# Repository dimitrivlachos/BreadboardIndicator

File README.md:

# Bread Board Indicator

This is a simple PCB design that adds a row of 30 LEDs to a breadboard in order to easily view microcontroller outputs (Or any outputs really).

## PCB
<table>
  <tr>
    <td></td><td></td>
  </tr>
 </table>

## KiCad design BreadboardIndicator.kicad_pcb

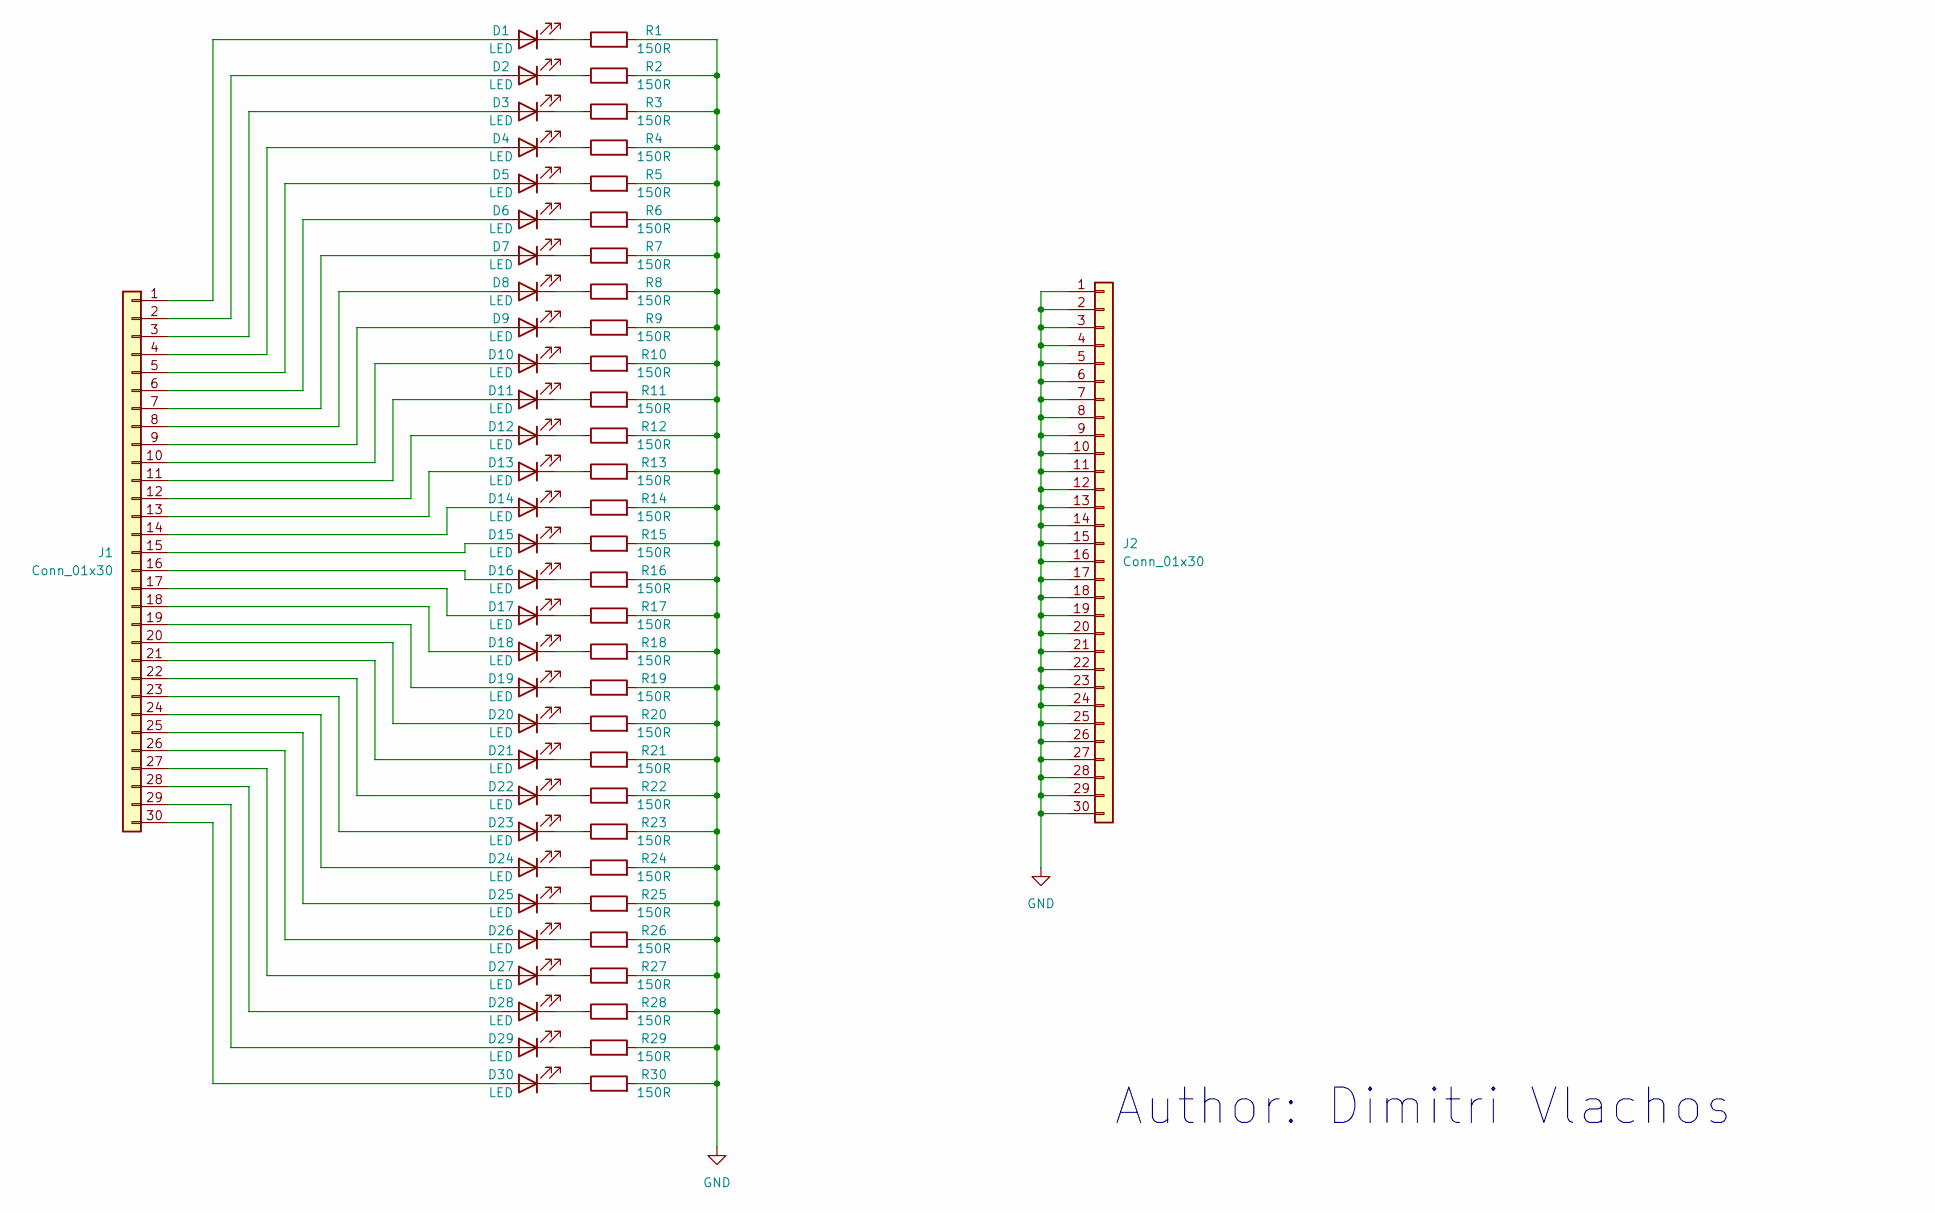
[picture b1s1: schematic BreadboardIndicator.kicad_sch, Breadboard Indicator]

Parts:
D1, D2, D3, D4, D5, D6, D7, D8, D9, D10, D11, D12, D13, D14, D15, D16, D17, D18, D19, D20, D21, D22, D23, D24, D25, D26, D27, D28, D29, D30: LED; LED_0805_2012Metric
J1, J2: Conn_01x30; PinHeader_1x30_P2.54mm_Vertical
R1, R2, R3, R4, R5, R6, R7, R8, R9, R10, R11, R12, R13, R14, R15, R16, R17, R18, R19, R20, R21, R22, R23, R24, R25, R26, R27, R28, R29, R30: 150R; R_0805_2012Metric

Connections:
GND: J2.1, J2.2, J2.3, J2.4, J2.5, J2.6, J2.7, J2.8, J2.9, J2.10, J2.11, J2.12, J2.13, J2.14, J2.15, J2.16, J2.17, J2.18, J2.19, J2.20, J2.21, J2.22, J2.23, J2.24, J2.25, J2.26, J2.27, J2.28, J2.29, J2.30, R1.2, R2.2, R3.2, R4.2, R5.2, R6.2, R7.2, R8.2, R9.2, R10.2, R11.2, R12.2, R13.2, R14.2, R15.2, R16.2, R17.2, R18.2, R19.2, R20.2, R21.2, R22.2, R23.2, R24.2, R25.2, R26.2, R27.2, R28.2, R29.2, R30.2; also elsewhere on the board
unnamed 1: D1.2 (A), J1.1; also elsewhere on the board
unnamed: D1.1 (K), R1.1
unnamed 3: D2.2 (A), J1.2; also elsewhere on the board
unnamed: D2.1 (K), R2.1
unnamed 5: D3.2 (A), J1.3; also elsewhere on the board
unnamed: D3.1 (K), R3.1
unnamed 7: D4.2 (A), J1.4; also elsewhere on the board
unnamed: D4.1 (K), R4.1
unnamed 9: D5.2 (A), J1.5; also elsewhere on the board
unnamed: D5.1 (K), R5.1
unnamed 11: D6.2 (A), J1.6; also elsewhere on the board
unnamed: D6.1 (K), R6.1
unnamed 13: D7.2 (A), J1.7; also elsewhere on the board
unnamed: D7.1 (K), R7.1
unnamed 15: D8.2 (A), J1.8; also elsewhere on the board
unnamed: D8.1 (K), R8.1
unnamed 17: D9.2 (A), J1.9; also elsewhere on the board
unnamed: D9.1 (K), R9.1
unnamed 19: D10.2 (A), J1.10; also elsewhere on the board
unnamed: D10.1 (K), R10.1
unnamed 21: D11.2 (A), J1.11; also elsewhere on the board
unnamed: D11.1 (K), R11.1
unnamed 23: D12.2 (A), J1.12; also elsewhere on the board
unnamed: D12.1 (K), R12.1
unnamed 25: D13.2 (A), J1.13; also elsewhere on the board
unnamed: D13.1 (K), R13.1
unnamed 27: D14.2 (A), J1.14; also elsewhere on the board
unnamed: D14.1 (K), R14.1
unnamed 29: D15.2 (A), J1.15; also elsewhere on the board
unnamed: D15.1 (K), R15.1
unnamed 31: D16.2 (A), J1.16; also elsewhere on the board
unnamed: D16.1 (K), R16.1
unnamed 33: D17.2 (A), J1.17; also elsewhere on the board
unnamed: D17.1 (K), R17.1
unnamed 35: D18.2 (A), J1.18; also elsewhere on the board
unnamed: D18.1 (K), R18.1
unnamed 37: D19.2 (A), J1.19; also elsewhere on the board
unnamed: D19.1 (K), R19.1
unnamed 39: D20.2 (A), J1.20; also elsewhere on the board
unnamed: D20.1 (K), R20.1
unnamed 41: D21.2 (A), J1.21; also elsewhere on the board
unnamed: D21.1 (K), R21.1
unnamed 43: D22.2 (A), J1.22; also elsewhere on the board
unnamed: D22.1 (K), R22.1
unnamed 45: D23.2 (A), J1.23; also elsewhere on the board
unnamed: D23.1 (K), R23.1
unnamed 47: D24.2 (A), J1.24; also elsewhere on the board
unnamed: D24.1 (K), R24.1
unnamed 49: D25.2 (A), J1.25; also elsewhere on the board
unnamed: D25.1 (K), R25.1
unnamed 51: D26.2 (A), J1.26; also elsewhere on the board
unnamed: D26.1 (K), R26.1
unnamed 53: D27.2 (A), J1.27; also elsewhere on the board
unnamed: D27.1 (K), R27.1
unnamed 55: D28.2 (A), J1.28; also elsewhere on the board
unnamed: D28.1 (K), R28.1
unnamed 57: D29.2 (A), J1.29; also elsewhere on the board
unnamed: D29.1 (K), R29.1
unnamed 59: D30.2 (A), J1.30; also elsewhere on the board
unnamed: D30.1 (K), R30.1

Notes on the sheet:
Author: Dimitri Vlachos

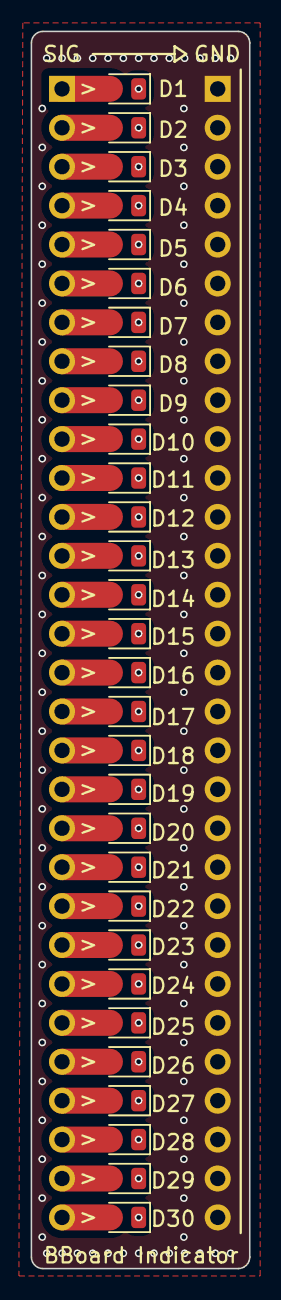
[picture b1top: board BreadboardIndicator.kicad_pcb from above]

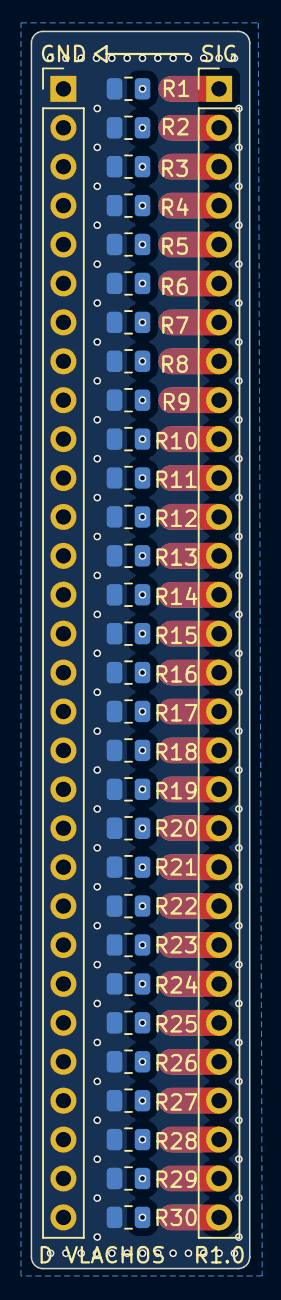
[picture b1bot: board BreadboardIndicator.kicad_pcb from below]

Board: 2 copper layers, 14.2 x 80.8 mm, 62 parts (32 on the bottom side), 61 nets.

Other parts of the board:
GND: Conn_01x30; PinHeader_1x30_P2.54mm_Vertical
SIG: Conn_01x30; PinHeader_1x30_P2.54mm_Vertical

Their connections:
GND: GND.1, GND.2, GND.3, GND.4, GND.5, GND.6, GND.7, GND.8, GND.9, GND.10, GND.11, GND.12, GND.13, GND.14, GND.15, GND.16, GND.17, GND.18, GND.19, GND.20, GND.21, GND.22, GND.23, GND.24, GND.25, GND.26, GND.27, GND.28, GND.29, GND.30; also elsewhere on the board
unnamed 1: SIG.1; also elsewhere on the board
unnamed 3: SIG.2; also elsewhere on the board
unnamed 5: SIG.3; also elsewhere on the board
unnamed 7: SIG.4; also elsewhere on the board
unnamed 9: SIG.5; also elsewhere on the board
unnamed 11: SIG.6; also elsewhere on the board
unnamed 13: SIG.7; also elsewhere on the board
unnamed 15: SIG.8; also elsewhere on the board
unnamed 17: SIG.9; also elsewhere on the board
unnamed 19: SIG.10; also elsewhere on the board
unnamed 21: SIG.11; also elsewhere on the board
unnamed 23: SIG.12; also elsewhere on the board
unnamed 25: SIG.13; also elsewhere on the board
unnamed 27: SIG.14; also elsewhere on the board
unnamed 29: SIG.15; also elsewhere on the board
unnamed 31: SIG.16; also elsewhere on the board
unnamed 33: SIG.17; also elsewhere on the board
unnamed 35: SIG.18; also elsewhere on the board
unnamed 37: SIG.19; also elsewhere on the board
unnamed 39: SIG.20; also elsewhere on the board
unnamed 41: SIG.21; also elsewhere on the board
unnamed 43: SIG.22; also elsewhere on the board
unnamed 45: SIG.23; also elsewhere on the board
unnamed 47: SIG.24; also elsewhere on the board
unnamed 49: SIG.25; also elsewhere on the board
unnamed 51: SIG.26; also elsewhere on the board
unnamed 53: SIG.27; also elsewhere on the board
unnamed 55: SIG.28; also elsewhere on the board
unnamed 57: SIG.29; also elsewhere on the board
unnamed 59: SIG.30; also elsewhere on the board

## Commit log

2024-04-20 Add Revision 1.0 to project
2024-04-20 Add example image
2024-04-20 Add schematic image
